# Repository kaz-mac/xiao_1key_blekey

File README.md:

# 1ボタンだけのワイヤレスキーボード for XIAO nRF52840
1ボタンしかないBLE接続のワイヤレスキーボードです。低消費電力のSeeed Studio XIAO nRF52840を使用し、CR2032コイン電池で駆動します。

関連ブログ
https://akibabara.com/blog/tag/1%e3%83%9c%e3%82%bf%e3%83%b3ble%e3%82%ad%e3%83%bc%e3%83%9c%e3%83%bc%e3%83%89

## 使用パーツ
* Seeed Studio [XIAO nRF52840](https://www.seeedstudio.com/Seeed-XIAO-BLE-nRF52840-p-5201.html)
* CR2032 Battery
* BC-2001 Battery-case
* original PCB
* Gateron KS-33 Low Profile Switch

## フォルダ一覧
|フォルダ|内容|
|---|---|
|src/|ソースプログラム|
|stl_case/|3Dプリントモデル　ケース|
|str_keycap/|3Dプリントモデル　キーキャップ|
|stl_soldermask/|3Dプリントモデル　ステンシル|
|pcb/|プリント基板(KiCad)|

## ライセンス
プログラムのソースコードはMITライセンスです。
3Dプリントモデルおよびプリント基板のデータはCC-BY-SAとします。
個別の表記がある場合はそれを優先します。

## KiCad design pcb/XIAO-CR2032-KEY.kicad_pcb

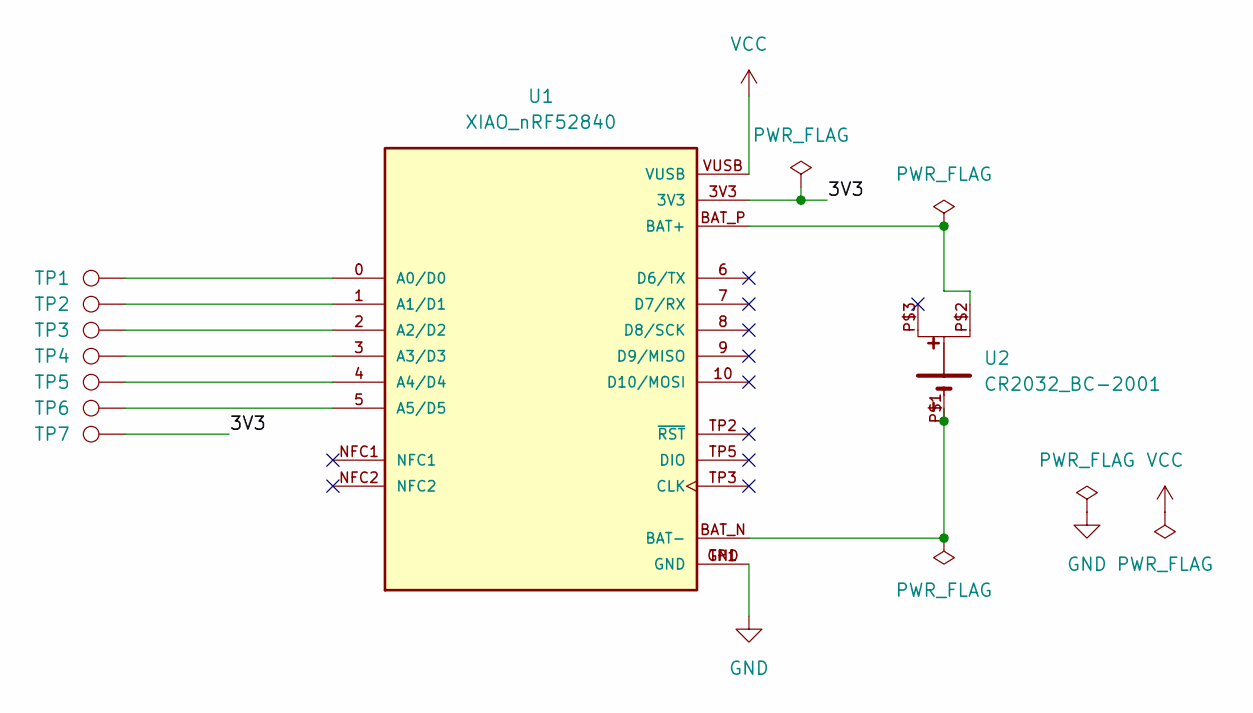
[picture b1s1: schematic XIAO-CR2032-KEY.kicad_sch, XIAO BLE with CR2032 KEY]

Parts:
TP1, TP2, TP3, TP4, TP5, TP6, TP7: TestPoint; TestPoint_Pad_1.5x1.5mm
U1: XIAO_nRF52840; XIAO_nRF52840_mini; PARTREV 2022/08/18
U2: CR2032_BC-2001; CR2032_BC-2001_cutting

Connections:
/3V3: TP7.1, U1.3V3
GND: U1.GND, U1.TP1 (GND)
unnamed: TP1.1, U1.0 (A0/D0)
unnamed: TP2.1, U1.1 (A1/D1)
unnamed: TP3.1, U1.2 (A2/D2)
unnamed: TP4.1, U1.3 (A3/D3)
unnamed: TP5.1, U1.4 (A4/D4)
unnamed: TP6.1, U1.5 (A5/D5)
unnamed: U1.BAT_P (BAT+), U2.P$2
unnamed: U1.BAT_N (BAT-), U2.P$1
VCC: U1.VUSB

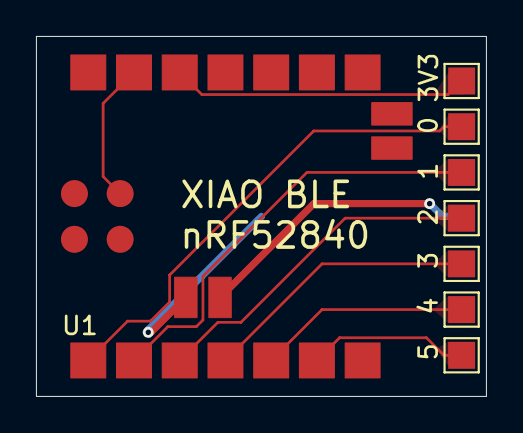
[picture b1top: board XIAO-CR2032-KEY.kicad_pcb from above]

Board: 2 copper layers, 25.0 x 20.0 mm, 9 parts (1 on the bottom side), 10 nets.
